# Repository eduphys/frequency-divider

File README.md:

# README

This repository contains the schematics and firmware for a frequency divider used in an experiment for time resolved transmission electron microscopy.
The frequency divider can operate up to 4 GHz and is optimized for low timing jitter. The jitter has not been determined by measurements, but calculations using the jiter of the individual components of the signal path lead to <5ps. The input is designed for 90-200mV pp.

The divider can be configured for a division factor of (2^a)(2^b) with a=0...3 and b=0...5.

## CAUTION:
The NB6N239S chip is not manufactured anymore. It is highly recommended to re-design the board!

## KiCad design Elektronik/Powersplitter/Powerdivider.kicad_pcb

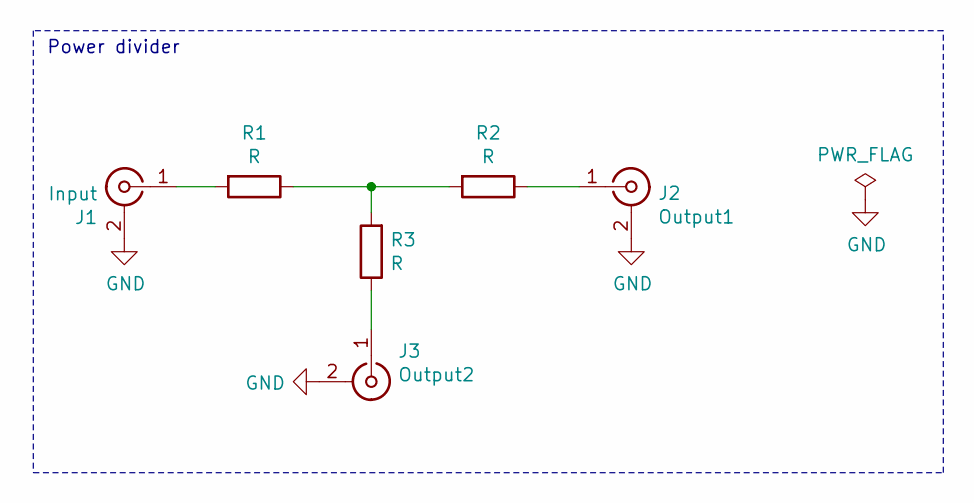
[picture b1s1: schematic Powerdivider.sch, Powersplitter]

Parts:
J1: Input; SMA_Amphenol_132289_EdgeMount
J2: Output1; SMA_Amphenol_132289_EdgeMount
J3: Output2; SMA_Amphenol_132289_EdgeMount
R1, R2, R3: R; R_0603_1608Metric_Pad1.05x0.95mm_HandSolder

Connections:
GND: J1.2 (Ext), J2.2 (Ext), J3.2 (Ext)
unnamed: J1.1 (In), R1.2
unnamed: J2.1 (In), R2.1
unnamed: J3.1 (In), R3.1
unnamed: R1.1, R2.2, R3.2

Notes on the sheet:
Power divider

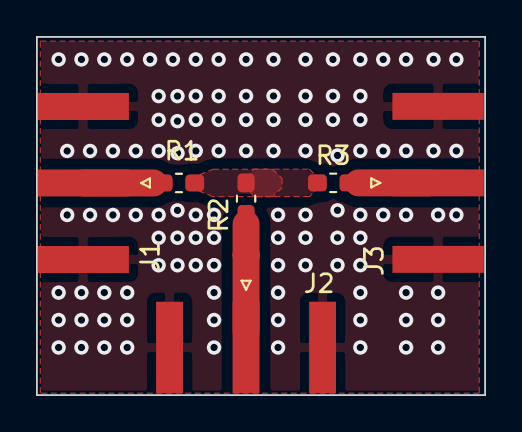
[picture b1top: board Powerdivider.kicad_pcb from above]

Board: 2 copper layers, 24.9 x 19.9 mm, 6 parts (0 on the bottom side), 5 nets.

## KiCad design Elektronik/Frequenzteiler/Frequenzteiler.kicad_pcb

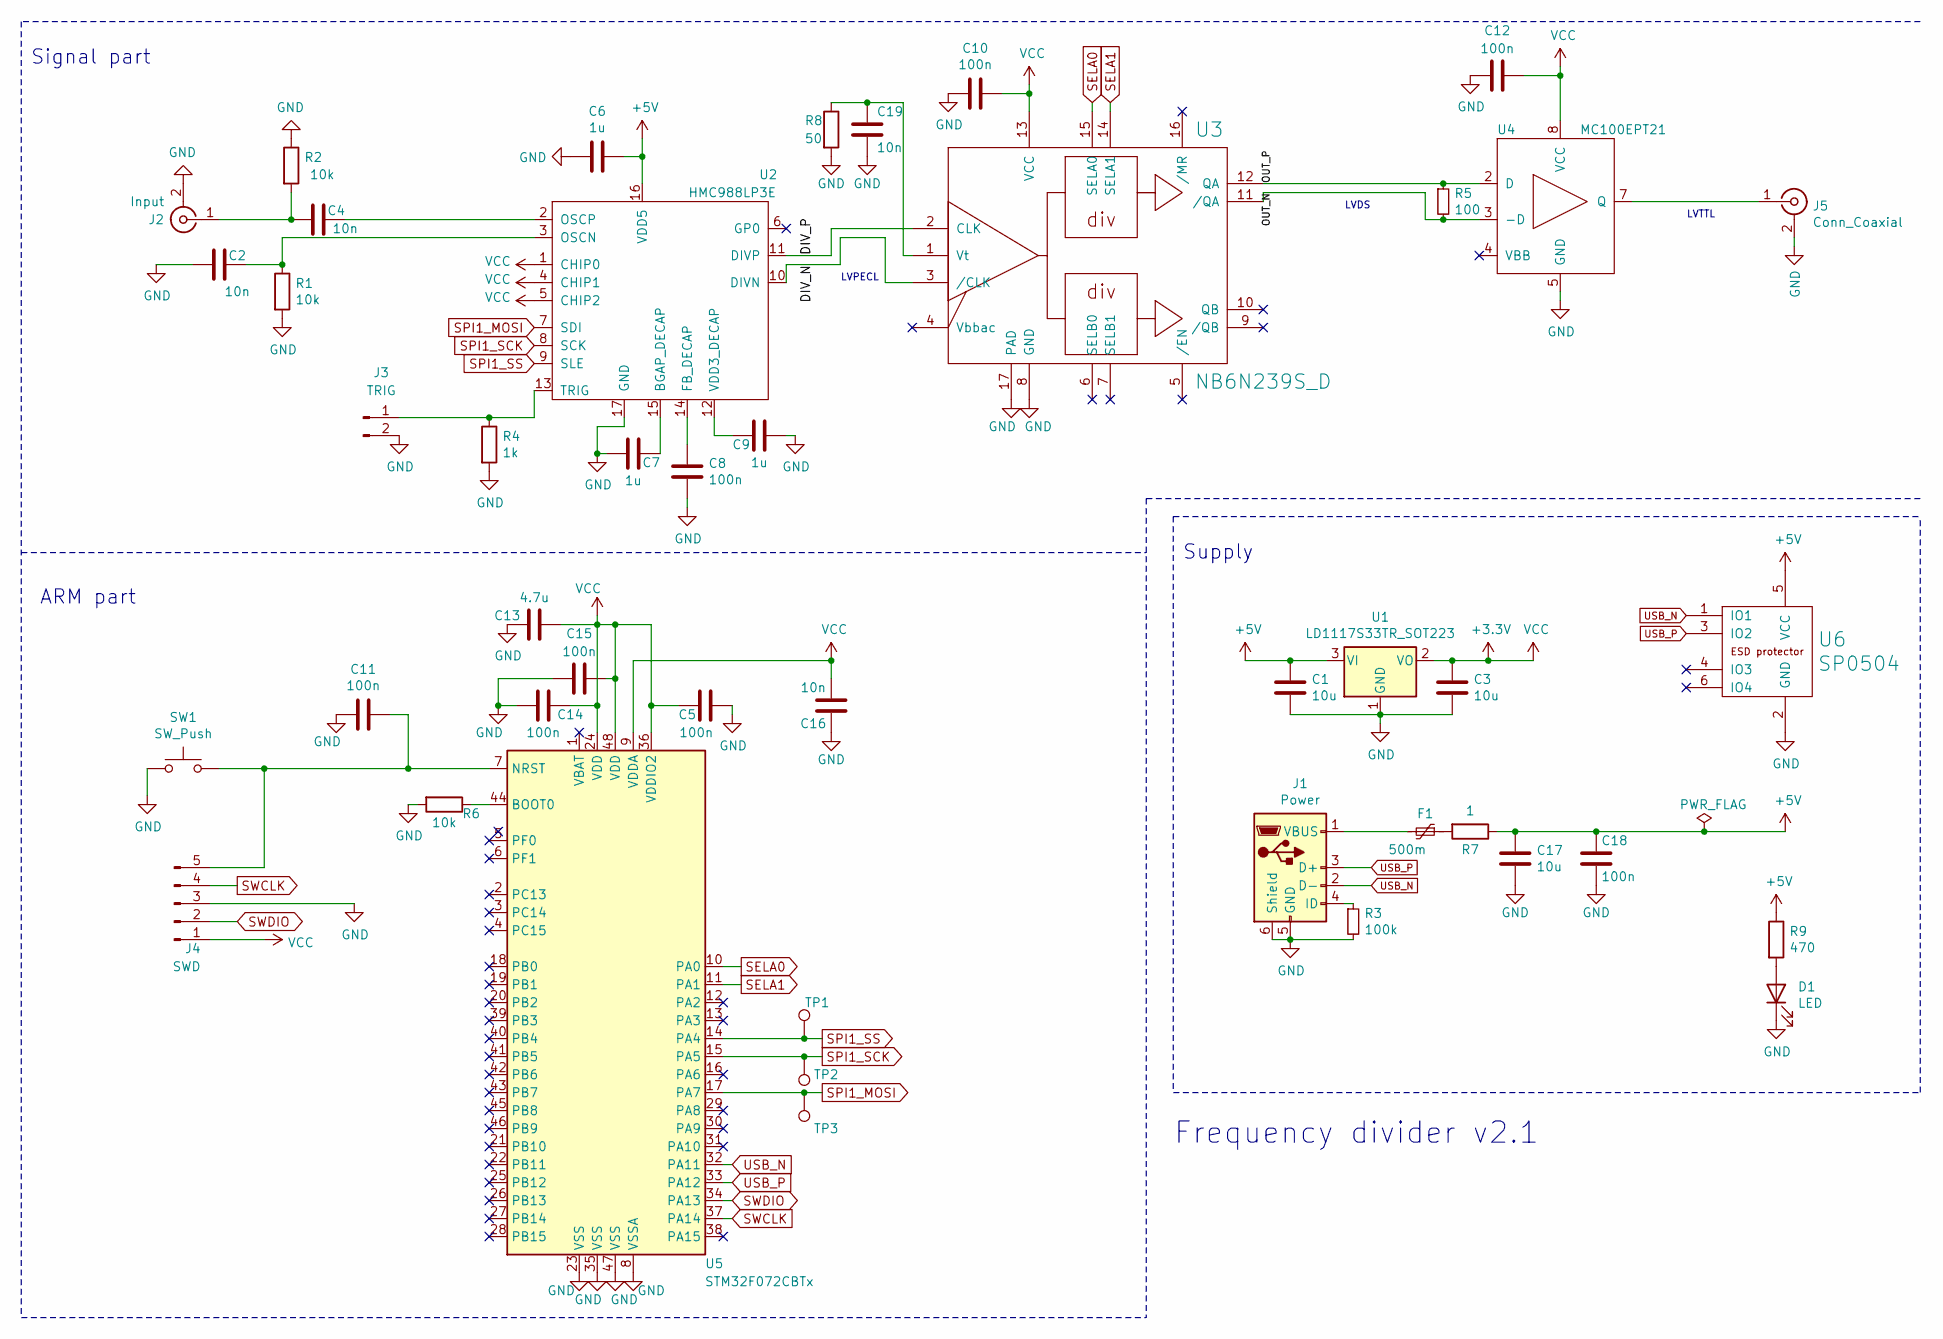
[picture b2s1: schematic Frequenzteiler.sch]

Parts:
C1, C3, C17: 10u; C_1206_3216Metric_Pad1.42x1.75mm_HandSolder
C2, C4, C16, C19: 10n; C_0603_1608Metric_Pad1.05x0.95mm_HandSolder
C5, C8, C10, C11, C12, C14, C15, C18: 100n; C_0603_1608Metric_Pad1.05x0.95mm_HandSolder
C6, C7, C9: 1u; C_0603_1608Metric_Pad1.05x0.95mm_HandSolder
C13: 4.7u; C_0805_2012Metric_Pad1.15x1.40mm_HandSolder
D1: LED; LED_0805_2012Metric_Pad1.15x1.40mm_HandSolder
F1: 500m; R_1206_3216Metric_Pad1.42x1.75mm_HandSolder
J1: Power; USB_Mini-B_Lumberg_2486_01_Horizontal
J2: Input; SMA_Amphenol_132289_EdgeMount
J3: TRIG; PinHeader_1x02_P2.54mm_Vertical
J4: SWD; PinHeader_1x05_P2.54mm_Vertical
J5: Conn_Coaxial; SMA_Amphenol_132289_EdgeMount
R1, R2, R6: 10k; R_0603_1608Metric_Pad1.05x0.95mm_HandSolder
R3: 100k; R_0603_1608Metric_Pad1.05x0.95mm_HandSolder
R4: 1k; R_0603_1608Metric_Pad1.05x0.95mm_HandSolder
R5: 100; R_0603_1608Metric_Pad1.05x0.95mm_HandSolder
R7: 1; R_0603_1608Metric_Pad1.05x0.95mm_HandSolder
R8: 50; R_0603_1608Metric_Pad1.05x0.95mm_HandSolder
R9: 470; R_0603_1608Metric_Pad1.05x0.95mm_HandSolder
SW1: SW_Push; SW_SPST_B3U-1000P
TP1, TP2, TP3: TestPoint; TestPoint_THTPad_D1.0mm_Drill0.5mm
U1: LD1117S33TR_SOT223; SOT-223-3_TabPin2
U2: HMC988LP3E; LFCSP-16-1EP_3x3mm_P0.5mm_EP1.854x1.854mm
U3: NB6N239S_D; LFCSP-16-1EP_3x3mm_P0.5mm_EP1.854x1.854mm
U4: MC100EPT21; TSSOP-8_3x3mm_P0.65mm
U5: STM32F072CBTx; LQFP-48_7x7mm_P0.5mm
U6: SP0504; SOT-23-6_Handsoldering

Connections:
+3V3: C3.1, C5.2, C10.1, C12.2, C13.1, C14.1, C15.1, C16.2, J4.1, U1.2 (VO), U2.1 (CHIP0), U2.4 (CHIP1), U2.5 (CHIP2), U3.13 (VCC), U4.8 (VCC), U5.9 (VDDA), U5.24 (VDD), U5.36 (VDDIO2), U5.48 (VDD)
+5V: C1.1, C6.1, C17.1, C18.1, R7.1, R9.1, U1.3 (VI), U2.16 (VDD5), U6.5 (VCC)
/DIV_N: U2.10 (DIVN), U3.3 (/CLK)
/DIV_P: U2.11 (DIVP), U3.2 (CLK)
/OUT_N: R5.2, U3.11 (/QA), U4.3 (-D)
/OUT_P: R5.1, U3.12 (QA), U4.2 (D)
GND: C1.2, C2.1, C3.2, C5.1, C6.2, C7.2, C8.2, C9.1, C10.2, C11.1, C12.1, C13.2, C14.2, C15.2, C16.1, C17.2, C18.2, C19.2, D1.1 (K), J1.5 (GND), J1.6 (Shield), J2.2 (Ext), J3.2, J4.3, J5.2 (Ext), R1.2, R2.1, R3.2, R4.2, R6.2, R8.2, SW1.1, U1.1 (GND), U2.17 (GND), U3.8 (GND), U3.17 (PAD), U4.5 (GND), U5.8 (VSSA), U5.23 (VSS), U5.35 (VSS), U5.47 (VSS), U6.2 (GND)
unnamed: C2.2, R1.1, U2.3 (OSCN)
unnamed: C4.1, U2.2 (OSCP)
unnamed: C4.2, J2.1 (In), R2.2
unnamed: C7.1, U2.15 (BGAP_DECAP)
unnamed: C8.1, U2.14 (FB_DECAP)
unnamed: C9.2, U2.12 (VDD3_DECAP)
unnamed: C11.2, J4.5, SW1.2, U5.7 (NRST)
unnamed: C19.1, R8.1, U3.1 (Vt)
unnamed: D1.2 (A), R9.2
unnamed: F1.1, R7.2
unnamed: F1.2, J1.1 (VBUS)
unnamed: J1.4 (ID), R3.1
unnamed: J3.1, R4.1, U2.13 (TRIG)
unnamed: J5.1 (In), U4.7 (Q)
unnamed: R6.1, U5.44 (BOOT0)
SELA0: U3.15 (SELA0), U5.10 (PA0)
SELA1: U3.14 (SELA1), U5.11 (PA1)
SPI1_MOSI: TP3.1, U2.7 (SDI), U5.17 (PA7)
SPI1_SCK: TP2.1, U2.8 (SCK), U5.15 (PA5)
SPI1_SS: TP1.1, U2.9 (SLE), U5.14 (PA4)
SWCLK: J4.4, U5.37 (PA14)
SWDIO: J4.2, U5.34 (PA13)
USB_N: J1.2 (D-), U5.32 (PA11), U6.1 (IO1)
USB_P: J1.3 (D+), U5.33 (PA12), U6.3 (IO2)

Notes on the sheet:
ARM part
Frequency divider v2.1
Signal part
Supply
LVPECL
LVDS
LVTTL

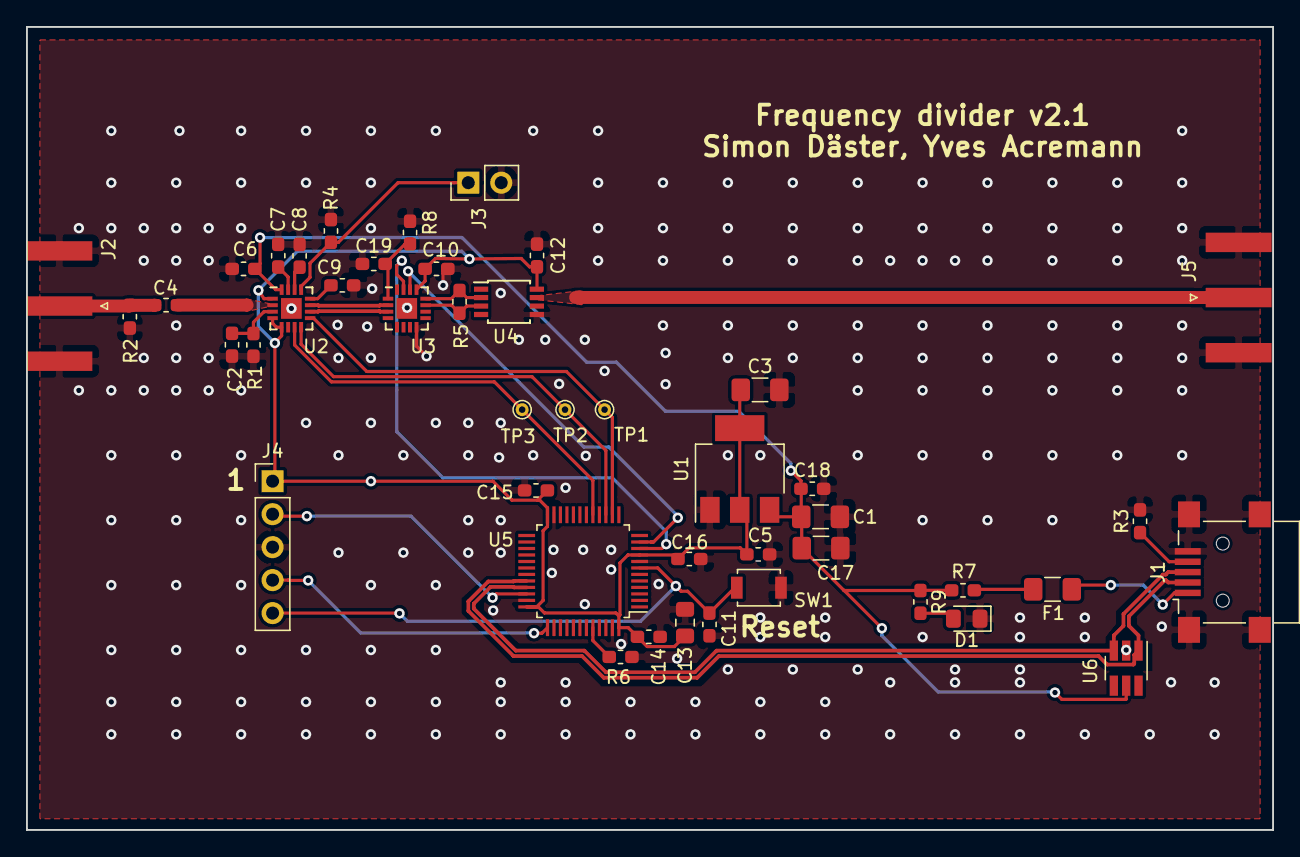
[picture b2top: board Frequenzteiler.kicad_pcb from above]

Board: 2 copper layers, 96.0 x 61.9 mm, 45 parts (0 on the bottom side), 31 nets.

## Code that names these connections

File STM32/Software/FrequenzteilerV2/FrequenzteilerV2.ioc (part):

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Mcu.Name=STM32F072C(8-B)Tx
Mcu.Package=LQFP48
Mcu.UserName=STM32F072CBTx
PA0.Signal=GPIO_Output
PA1.Signal=GPIO_Output
PA11.Mode=Device
PA11.Signal=USB_DM
PA12.Mode=Device
PA12.Signal=USB_DP
PA13.Mode=Serial_Wire
PA13.Signal=SYS_SWDIO
PA14.Mode=Serial_Wire
PA14.Signal=SYS_SWCLK
PA4.Mode=NSS_Signal_Hard_Output
PA4.Signal=SPI1_NSS
PA5.Mode=TX_Only_Simplex_Unidirect_Master
PA5.Signal=SPI1_SCK
PA7.Mode=TX_Only_Simplex_Unidirect_Master
PA7.Signal=SPI1_MOSI
RCC.SYSCLKFreq_VALUE=48000000
RCC.SYSCLKSource=RCC_SYSCLKSOURCE_HSI48
board=custom

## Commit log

2021-08-06 Added Electronics
2021-08-06 Added STM32 project files and code
2021-08-06 Added TANGO files
2021-08-06 Added .gitignore and a empty README
